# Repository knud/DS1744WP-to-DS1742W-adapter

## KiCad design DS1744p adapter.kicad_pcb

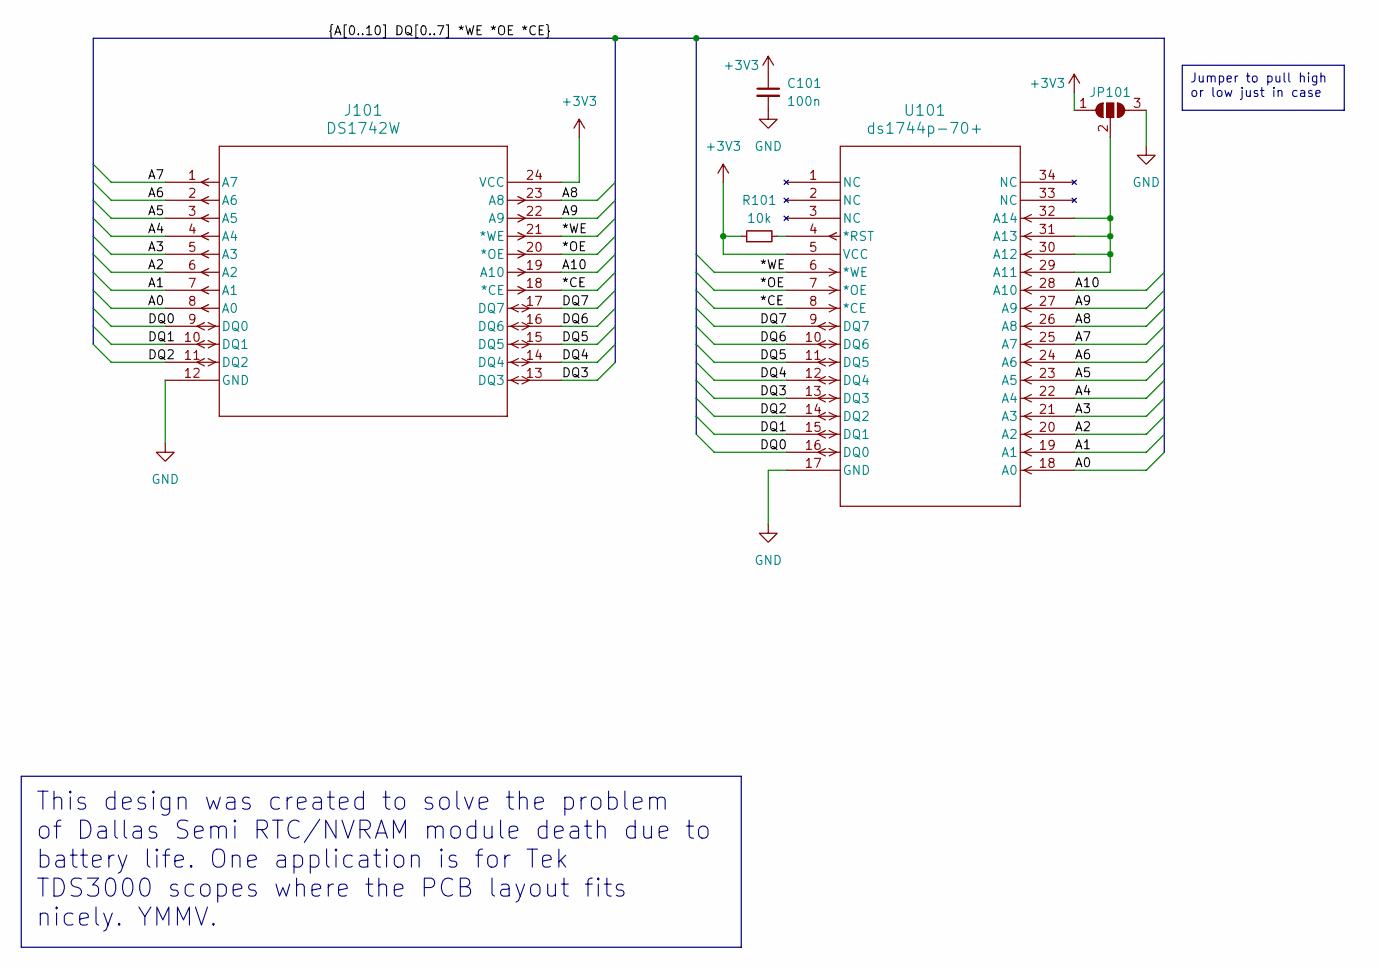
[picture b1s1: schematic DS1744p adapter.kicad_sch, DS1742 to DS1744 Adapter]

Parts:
C101: 100n; C_0603_1608Metric_Pad1.08x0.95mm_HandSolder
J101: DS1742W; DIP-24_W15.24mm_LongPads
JP101: SolderJumper-3_P1.3mm_Open_RoundedPad1.0x1.5mm
R101: 10k; R_0603_1608Metric_Pad0.98x0.95mm_HandSolder
U101: ds1744p-70+; 21-0246_PC2&plus_2_MXM

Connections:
+3V3: C101.1, J101.24 (VCC), JP101.1 (A), R101.1, U101.5 (VCC)
/*CE: J101.18 (*CE), U101.8 (*CE)
/*OE: J101.20 (*OE), U101.7 (*OE)
/*WE: J101.21 (*WE), U101.6 (*WE)
/A0: J101.8 (A0), U101.18 (A0)
/A1: J101.7 (A1), U101.19 (A1)
/A2: J101.6 (A2), U101.20 (A2)
/A3: J101.5 (A3), U101.21 (A3)
/A4: J101.4 (A4), U101.22 (A4)
/A5: J101.3 (A5), U101.23 (A5)
/A6: J101.2 (A6), U101.24 (A6)
/A7: J101.1 (A7), U101.25 (A7)
/A8: J101.23 (A8), U101.26 (A8)
/A9: J101.22 (A9), U101.27 (A9)
/A10: J101.19 (A10), U101.28 (A10)
/DQ0: J101.9 (DQ0), U101.16 (DQ0)
/DQ1: J101.10 (DQ1), U101.15 (DQ1)
/DQ2: J101.11 (DQ2), U101.14 (DQ2)
/DQ3: J101.13 (DQ3), U101.13 (DQ3)
/DQ4: J101.14 (DQ4), U101.12 (DQ4)
/DQ5: J101.15 (DQ5), U101.11 (DQ5)
/DQ6: J101.16 (DQ6), U101.10 (DQ6)
/DQ7: J101.17 (DQ7), U101.9 (DQ7)
GND: C101.2, J101.12 (GND), JP101.3 (B), U101.17 (GND)
unnamed: JP101.2 (C), U101.29 (A11), U101.30 (A12), U101.31 (A13), U101.32 (A14)
unnamed: R101.2, U101.4 (*RST)

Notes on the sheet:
This design was created to solve the problem of Dallas Semi RTC/NVRAM module death due to battery life. One application is for Tek TDS3000 scopes where the PCB layout fits nicely. YMMV.
Jumper to pull high or low just in case

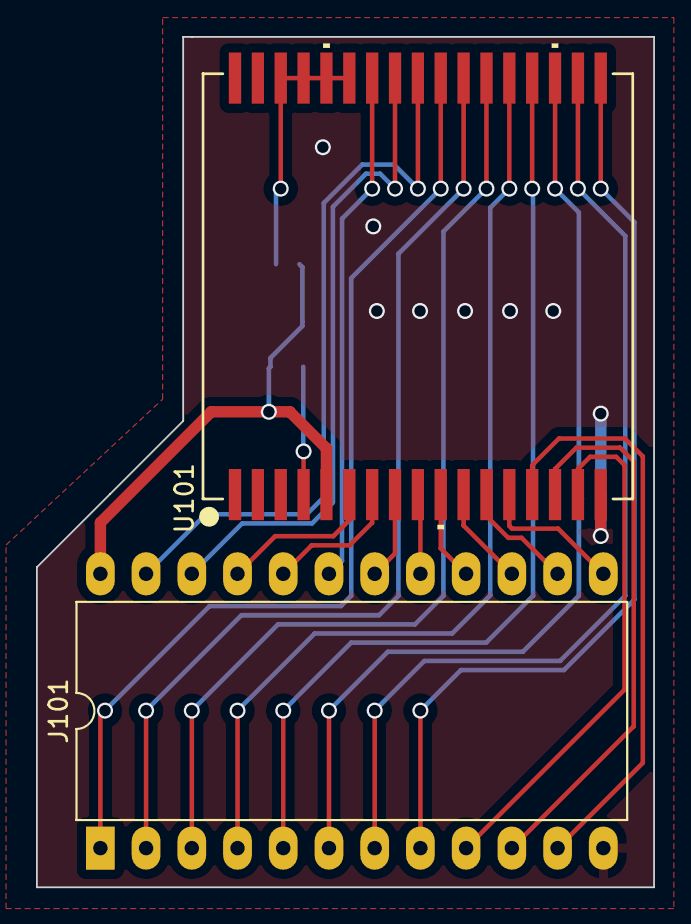
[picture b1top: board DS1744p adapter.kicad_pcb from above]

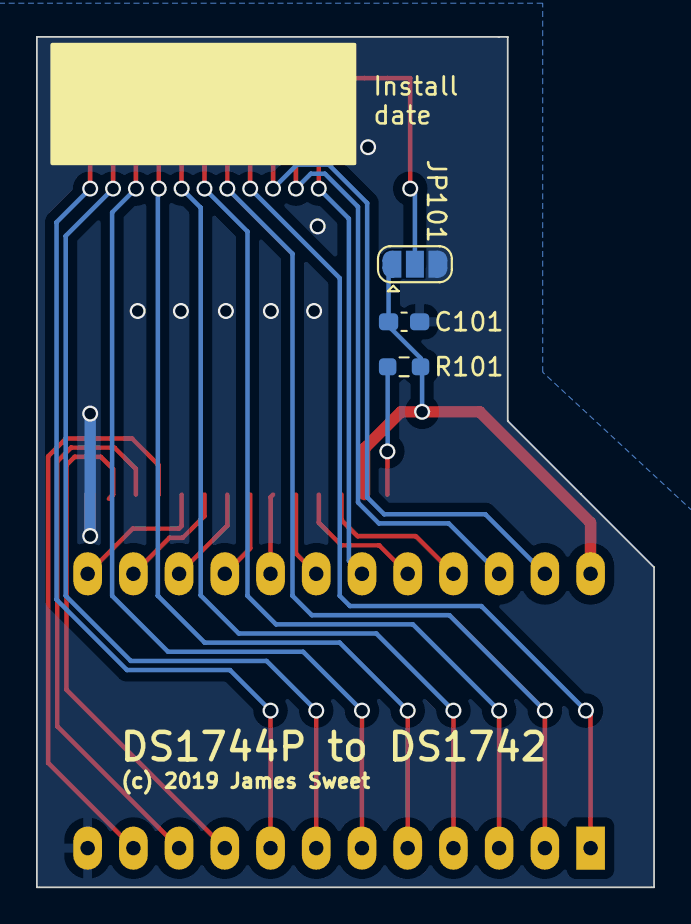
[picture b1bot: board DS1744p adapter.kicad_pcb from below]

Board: 2 copper layers, 34.3 x 47.2 mm, 5 parts (3 on the bottom side), 26 nets.

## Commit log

2023-11-27 cleaned up and updated for KiCAD 7
2025-08-21 update for rescue dir
2025-08-21 update? Why is this here as .gitignore says no...
2025-08-21 clean up
2025-08-21 remove rescue backup

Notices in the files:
DS1744p adapter.kicad_pcb:
(c) 2019 James Sweet
DS1744p adapter.kicad_sch:
License : GPL-3.0
